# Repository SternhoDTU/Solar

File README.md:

# Solar
Depository for my work on the DTU solar car

Currently has:
- A pcb and schematic for a testbench in KiCAD 8.0 (CAN_TESTBENCH)
- STM 32 code for a receiver tailored to receive CAN signals from the speeder see this [link](https://kvaser.com/support/calculators/can-fd-bit-timing-calculator/?v=0.12&nbr=500000&dbr=1000000&nsjw=4&dtps1=5&dtps2=2&f=48000&t=50&d=200&np=1&dp=4&f=200000&t=50&d=200&np=1&dp=5) for timing calculations

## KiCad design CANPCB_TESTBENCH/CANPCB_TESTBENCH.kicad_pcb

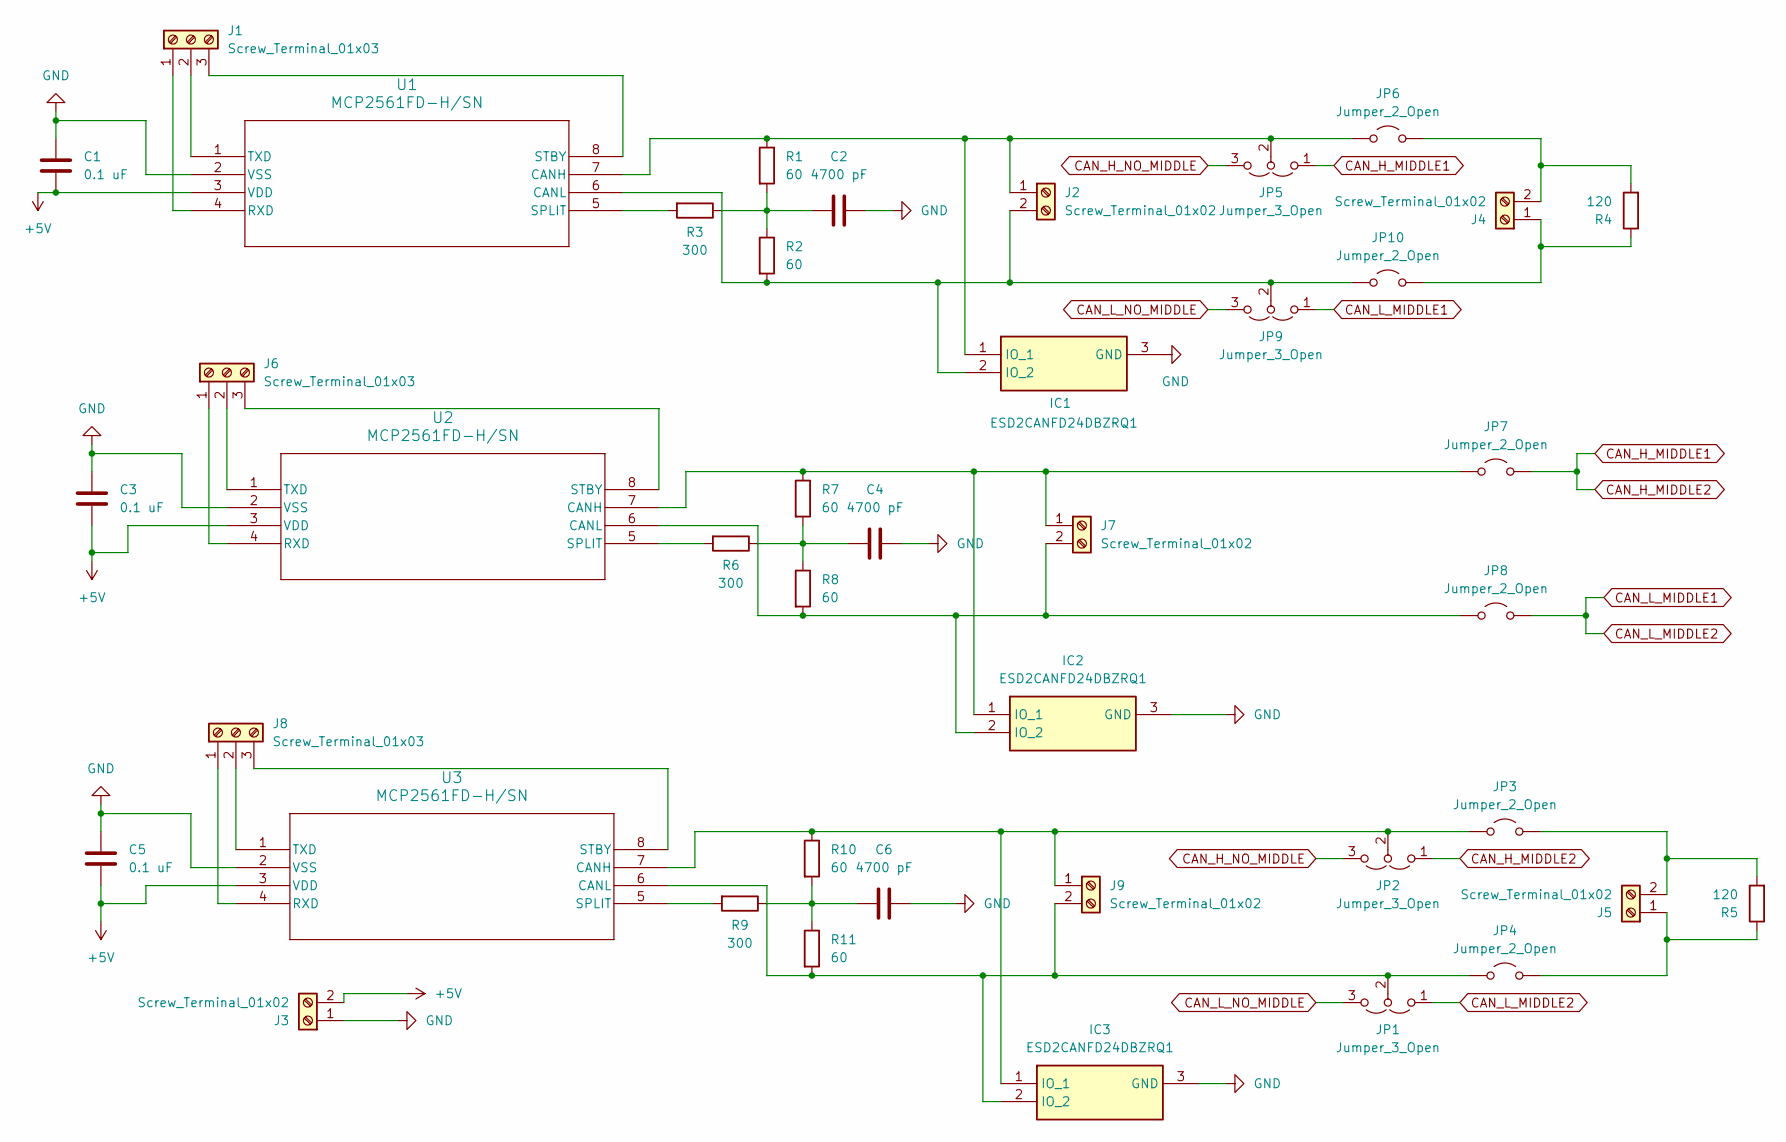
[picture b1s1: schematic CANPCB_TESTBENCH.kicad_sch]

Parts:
C1, C3, C5: 0.1 uF; C_0603_1608Metric
C2, C4, C6: 4700 pF; C_0603_1608Metric
IC1, IC2, IC3: ESD2CANFD24DBZRQ1; SOT95P237X112-3N; Manufacturer_Part_Number ESD2CANFD24DBZRQ1
J1, J6, J8: Screw_Terminal_01x03; TerminalBlock_Phoenix_MPT-0,5-3-2.54_1x03_P2.54mm_Horizontal
J2, J3, J4, J5, J7, J9: Screw_Terminal_01x02; TerminalBlock_Phoenix_MPT-0,5-2-2.54_1x02_P2.54mm_Horizontal
JP1, JP2, JP5, JP9: Jumper_3_Open; 61300311121
JP3, JP4, JP6, JP7, JP8, JP10: Jumper_2_Open; 61300211121
R1, R2, R7, R8, R10, R11: 60; R_0603_1608Metric
R3, R6, R9: 300; R_0603_1608Metric
R4, R5: 120; R_0603_1608Metric
U1, U2, U3: MCP2561FD-H/SN; SOIC8-N_MC_MCH

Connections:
+5V: C1.2, C3.2, C5.2, J3.2, U1.3 (VDD), U2.3 (VDD), U3.3 (VDD)
CAN_H_MIDDLE1: JP2.1 (A), JP5.1 (A), JP7.2 (B)
CAN_H_NO_MIDDLE: JP2.3 (B), JP5.3 (B)
CAN_L_MIDDLE1: JP1.1 (A), JP8.2 (B), JP9.1 (A)
CAN_L_NO_MIDDLE: JP1.3 (B), JP9.3 (B)
GND: C1.1, C2.2, C3.1, C4.2, C5.1, C6.2, IC1.3 (GND), IC2.3 (GND), IC3.3 (GND), J3.1, U1.2 (VSS), U2.2 (VSS), U3.2 (VSS)
unnamed: C2.1, R1.2, R2.1, R3.1
unnamed: C4.1, R6.1, R7.2, R8.1
unnamed: C6.1, R9.1, R10.2, R11.1
unnamed: IC1.1 (IO_1), J2.1, JP5.2 (C), JP6.1 (A), R1.1, U1.7 (CANH)
unnamed: IC1.2 (IO_2), J2.2, JP9.2 (C), JP10.1 (A), R2.2, U1.6 (CANL)
unnamed: IC2.1 (IO_1), J7.1, JP7.1 (A), R7.1, U2.7 (CANH)
unnamed: IC2.2 (IO_2), J7.2, JP8.1 (A), R8.2, U2.6 (CANL)
unnamed: IC3.1 (IO_1), J9.1, JP2.2 (C), JP3.1 (A), R10.1, U3.7 (CANH)
unnamed: IC3.2 (IO_2), J9.2, JP1.2 (C), JP4.1 (A), R11.2, U3.6 (CANL)
unnamed: J1.1, U1.4 (RXD)
unnamed: J1.2, U1.1 (TXD)
unnamed: J1.3, U1.8 (STBY)
unnamed: J4.1, JP10.2 (B), R4.1
unnamed: J4.2, JP6.2 (B), R4.2
unnamed: J5.1, JP4.2 (B), R5.1
unnamed: J5.2, JP3.2 (B), R5.2
unnamed: J6.1, U2.4 (RXD)
unnamed: J6.2, U2.1 (TXD)
unnamed: J6.3, U2.8 (STBY)
unnamed: J8.1, U3.4 (RXD)
unnamed: J8.2, U3.1 (TXD)
unnamed: J8.3, U3.8 (STBY)
unnamed: R3.2, U1.5 (SPLIT)
unnamed: R6.2, U2.5 (SPLIT)
unnamed: R9.2, U3.5 (SPLIT)

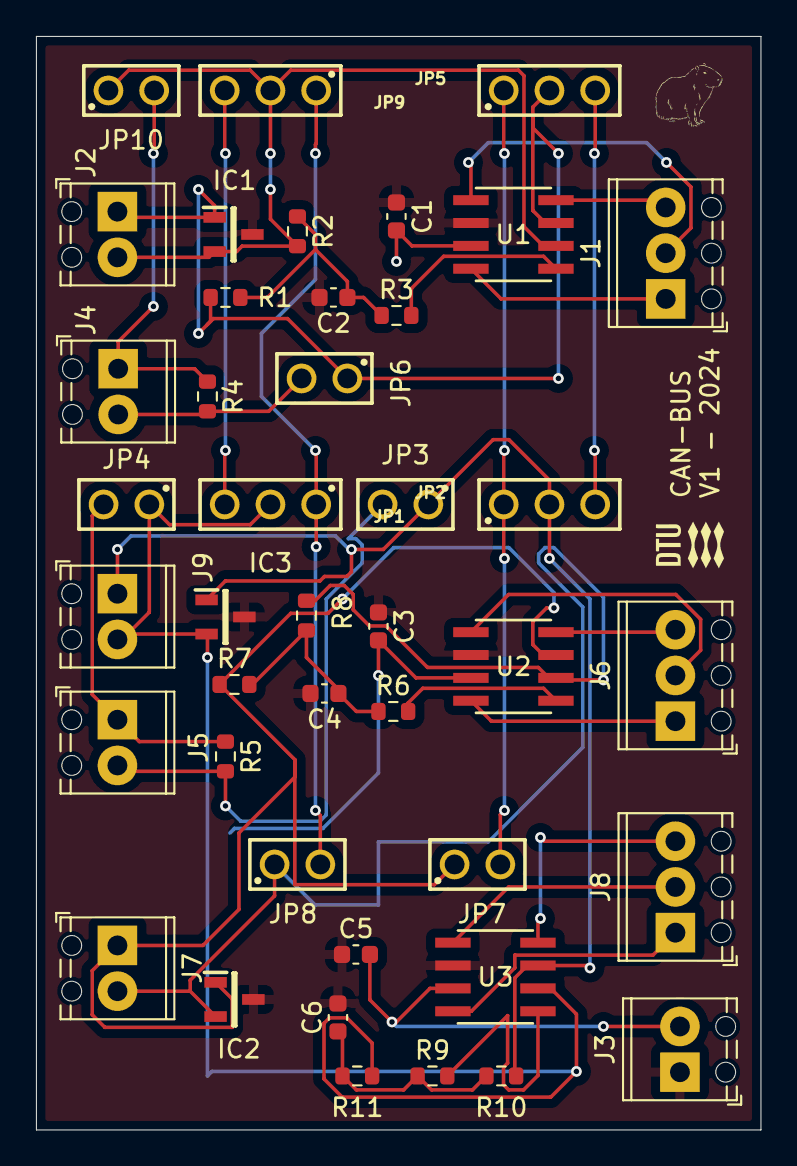
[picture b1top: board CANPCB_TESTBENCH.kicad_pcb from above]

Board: 2 copper layers, 40.2 x 60.8 mm, 42 parts (0 on the bottom side), 31 nets.

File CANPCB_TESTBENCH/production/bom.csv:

Designator,Footprint,Quantity,Value,LCSC Part #
"C1, C3, C5",0603,3,0.1 uF,
"C2, C4, C6",0603,3,4700 pF,
"IC1, IC2, IC3",SOT95P237X112-3N,3,ESD2CANFD24DBZRQ1,
"J1, J6, J8","TerminalBlock_Phoenix_MPT-0,5-3-2.54_1x03_P2.54mm_Horizontal",3,Screw_Terminal_01x03,
"J2, J3, J4, J5, J7, J9","TerminalBlock_Phoenix_MPT-0,5-2-2.54_1x02_P2.54mm_Horizontal",6,Screw_Terminal_01x02,
"JP1, JP2, JP5, JP9",61300311121,4,Jumper_3_Open,
"JP10, JP3, JP4, JP6, JP7, JP8",61300211121,6,Jumper_2_Open,
"R1, R10, R11, R2, R7, R8",0603,6,60,
"R3, R6, R9",0603,3,300,
"R4, R5",0603,2,120,
"U1, U2, U3",SOIC8-N_MC_MCH,3,MCP2561FD-H/SN,

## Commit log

2025-05-14 Add files via upload
    KICAD 8.0 shcematic and pcb for the CAN testbench
2025-05-14 Add FDCAN_Classic_Frame_Networking folder to repo
2025-05-14 Add FDCAN_Classic_Frame_Networking folder as normal directory
2025-05-14 Add FDCAN_Classic_Frame_Networking as regular folder (not submodule)
2025-05-14 Finally add FDCAN_Classic_Frame_Networking as real folder
2025-06-11 Create here
2025-06-11 Update and rename here to j
